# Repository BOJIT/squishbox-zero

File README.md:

# squishbox-zero
MIDI Synthesiser based on https://github.com/GeekFunkLabs/squishbox: adapted for Pi Zero 2W

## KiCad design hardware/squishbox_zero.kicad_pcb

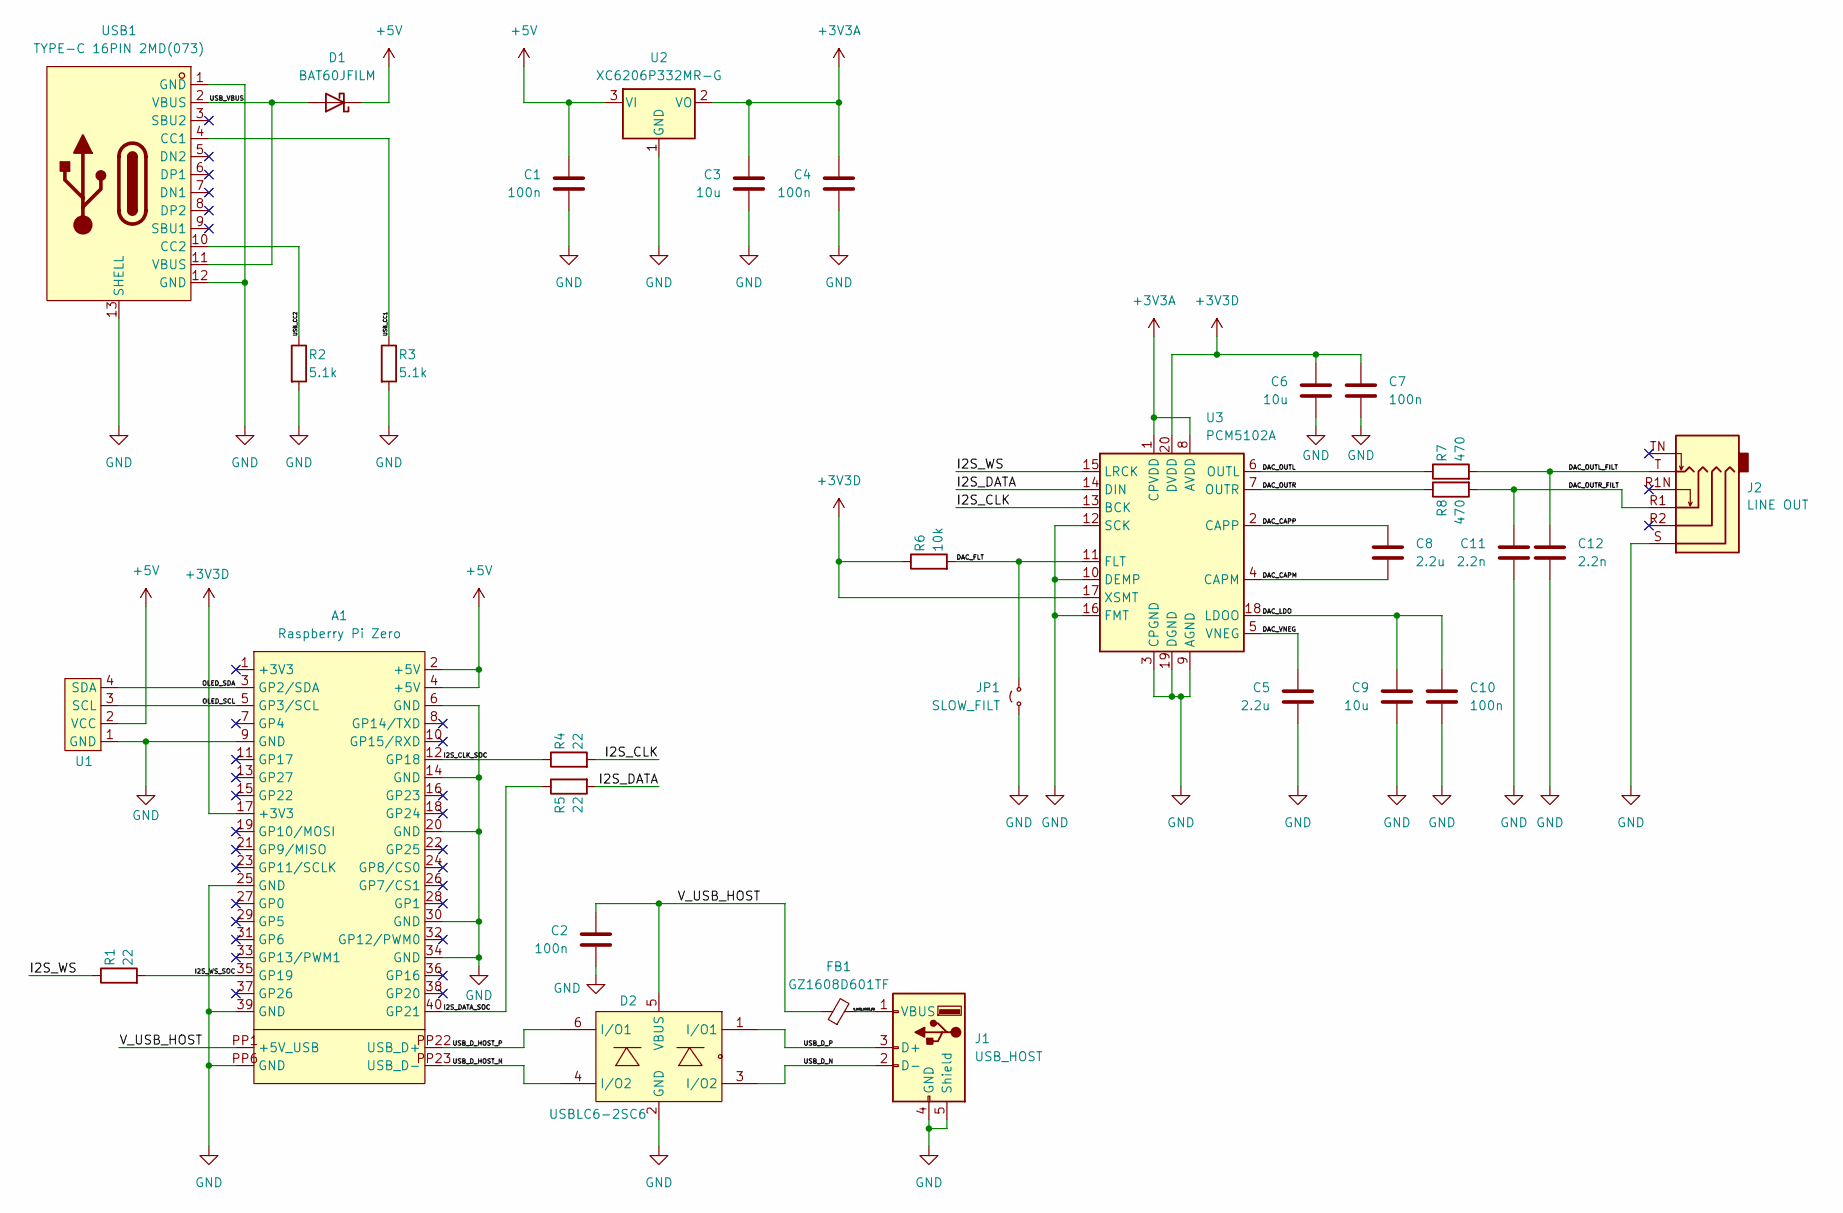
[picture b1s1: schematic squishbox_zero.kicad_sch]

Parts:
A1: Raspberry Pi Zero; Raspberry_Pi_Zero
C1, C2, C4, C7, C10: 100n; C_0402_1005Metric; LCSC Part C1525
C3, C6, C9: 10u; C_0603_1608Metric; LCSC Part C19702
C5, C8: 2.2u; C_0402_1005Metric; LCSC Part C12530
C11, C12: 2.2n; C_0805_2012Metric; LCSC Part C28260
D1: BAT60JFILM; D_SOD-323; LCSC Part C133103
D2: USBLC6-2SC6; SOT-23-6_L2.9-W1.6-P0.95-LS2.8-BL; LCSC Part C7519
FB1: GZ1608D601TF; R_0603_1608Metric; LCSC Part C1002
J1: USB_HOST; USB-A-SMD_USB-M-21; LCSC Part C42474
J2: LINE OUT; AUDIO-SMD_PJ-342; LCSC Part C668606
JP1: SLOW_FILT; SolderJumper-2_P1.3mm_Open_RoundedPad1.0x1.5mm
R1, R4, R5: 22; R_0402_1005Metric; LCSC Part C25092
R2, R3: 5.1k; R_0402_1005Metric; LCSC Part C25905
R6: 10k; R_0402_1005Metric; LCSC Part C25744
R7, R8: 470; R_0402_1005Metric; LCSC Part C25117
U1: SSD1306-0.91-OLED-4pin-128x32
U2: XC6206P332MR-G; SOT-23-3; LCSC Part C5446
U3: PCM5102A; TSSOP-20_4.4x6.5mm_P0.65mm; LCSC Part C107671
USB1: TYPE-C 16PIN 2MD(073); USB-C-SMD_TYPE-C-16PIN; LCSC Part C2765186

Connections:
+3V3A: C3.1, C4.1, U2.2 (VO), U3.1 (CPVDD), U3.8 (AVDD)
+3V3D: A1.17 (+3V3), C6.1, C7.1, R6.1, U3.17 (XSMT), U3.20 (DVDD)
+5V: A1.2 (+5V), A1.4 (+5V), C1.1, D1.1 (K), U1.2 (VCC), U2.3 (VI)
/DAC_CAPM: C8.2, U3.4 (CAPM)
/DAC_CAPP: C8.1, U3.2 (CAPP)
/DAC_FLT: JP1.2 (B), R6.2, U3.11 (FLT)
/DAC_LDO: C9.1, C10.1, U3.18 (LDOO)
/DAC_OUTL: R7.1, U3.6 (OUTL)
/DAC_OUTL_FILT: C12.1, J2.T, R7.2
/DAC_OUTR: R8.1, U3.7 (OUTR)
/DAC_OUTR_FILT: C11.1, J2.R1, R8.2
/DAC_VNEG: C5.1, U3.5 (VNEG)
/I2S_CLK: R4.2, U3.13 (BCK)
/I2S_CLK_SOC: A1.12 (GP18), R4.1
/I2S_DATA: R5.2, U3.14 (DIN)
/I2S_DATA_SOC: A1.40 (GP21), R5.1
/I2S_WS: R1.1, U3.15 (LRCK)
/I2S_WS_SOC: A1.35 (GP19), R1.2
/OLED_SCL: A1.5 (GP3/SCL), U1.3 (SCL)
/OLED_SDA: A1.3 (GP2/SDA), U1.4 (SDA)
/USB_CC1: R3.1, USB1.4 (CC1)
/USB_CC2: R2.1, USB1.10 (CC2)
/USB_D_HOST_N: A1.PP23 (USB_D-), D2.4 (I/O2)
/USB_D_HOST_P: A1.PP22 (USB_D+), D2.6 (I/O1)
/USB_D_N: D2.3 (I/O2), J1.2 (D-)
/USB_D_P: D2.1 (I/O1), J1.3 (D+)
/USB_VBUS: D1.2 (A), USB1.2 (VBUS), USB1.11 (VBUS)
/V_USB_HOST: A1.PP1 (+5V_USB), C2.1, D2.5 (VBUS), FB1.1
/V_USB_HOST_FB: FB1.2, J1.1 (VBUS)
GND: A1.6 (GND), A1.9 (GND), A1.14 (GND), A1.20 (GND), A1.25 (GND), A1.30 (GND), A1.34 (GND), A1.39 (GND), A1.PP6 (GND), C1.2, C2.2, C3.2, C4.2, C5.2, C6.2, C7.2, C9.2, C10.2, C11.2, C12.2, D2.2 (GND), J1.4 (GND), J1.5 (Shield), J2.S, JP1.1 (A), R2.2, R3.2, U1.1 (GND), U2.1 (GND), U3.3 (CPGND), U3.9 (AGND), U3.10 (DEMP), U3.12 (SCK), U3.16 (FMT), U3.19 (DGND), USB1.1 (GND), USB1.12 (GND), USB1.13 (SHELL)

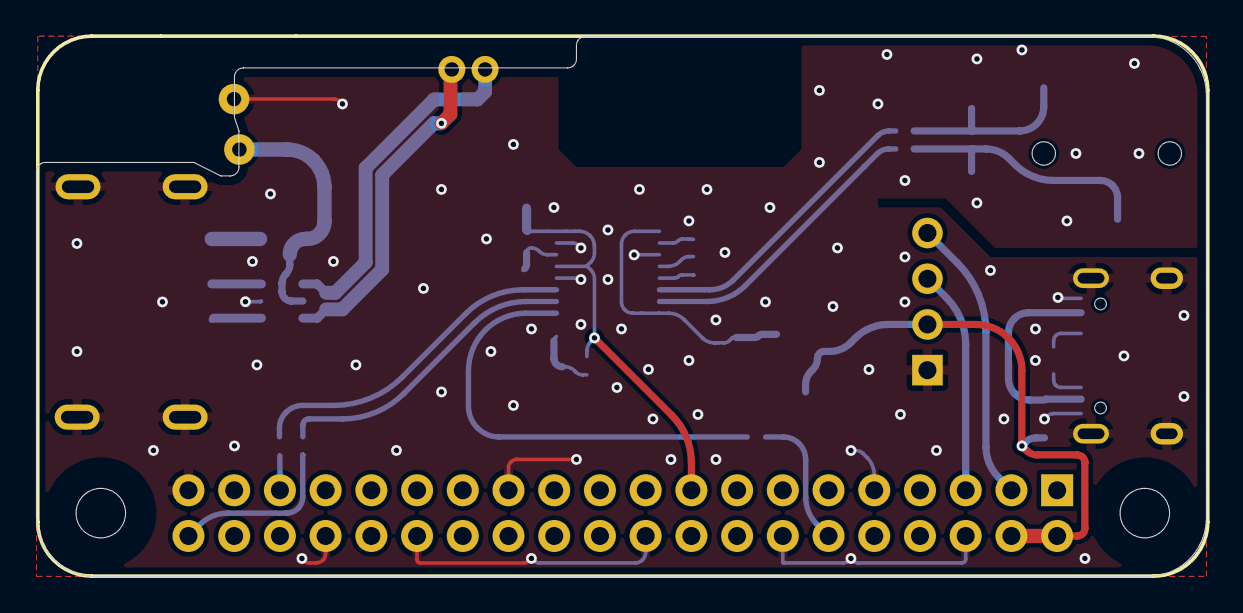
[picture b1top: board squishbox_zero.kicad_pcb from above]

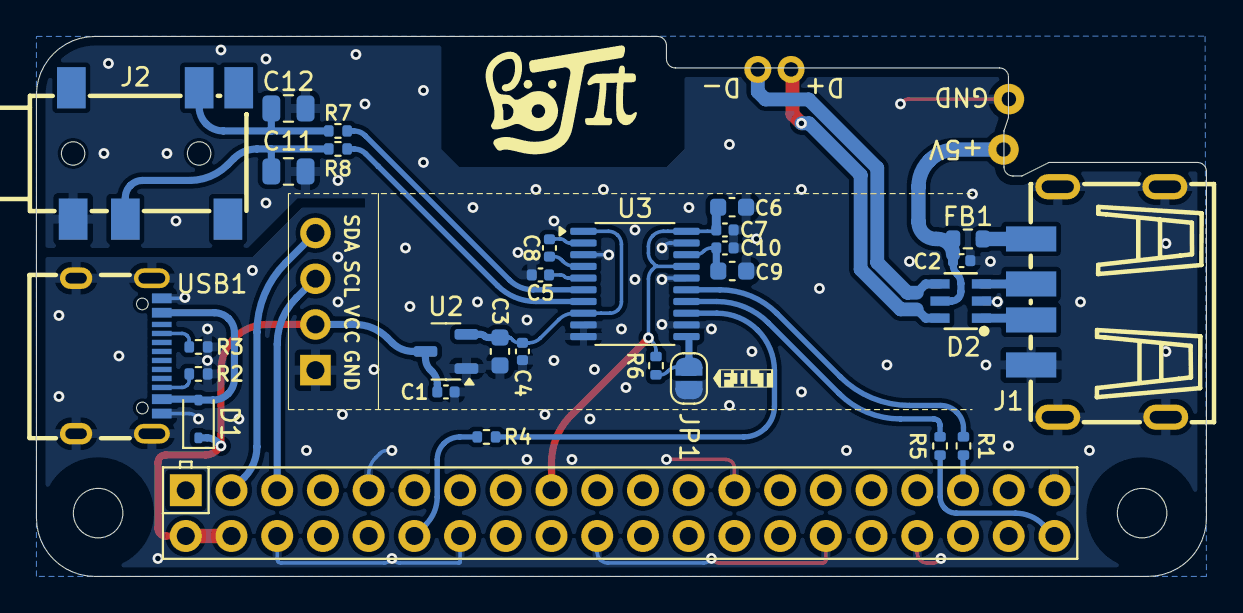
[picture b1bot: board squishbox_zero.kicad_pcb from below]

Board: 2 copper layers, 65.0 x 30.0 mm, 32 parts (32 on the bottom side), 30 nets.

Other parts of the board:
kibuzzard-68B38B7F: G***; kibuzzard-68B38B7F

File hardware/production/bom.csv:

Designator           , Footprint                        , Quantity, Value                , LCSC Part #
"C1, C10, C2, C4, C7", 0402                             ,        5, 100n                 , C1525
"C11, C12"           , 0805                             ,        2, 2.2n                 , C28260
"C3, C6, C9"         , 0603                             ,        3, 10u                  , C19702
"C5, C8"             , 0402                             ,        2, 2.2u                 , C12530
D1                   , D_SOD-323                        ,        1, BAT60JFILM           , C133103
D2                   , SOT-23-6_L2.9-W1.6-P0.95-LS2.8-BL,        1, USBLC6-2SC6          , C7519
FB1                  , 0603                             ,        1, GZ1608D601TF         , C1002
J1                   , USB-A-SMD_USB-M-21               ,        1, USB_HOST             , C42474
J2                   , AUDIO-SMD_PJ-342                 ,        1, LINE OUT             , C668606
"R1, R4, R5"         , 0402                             ,        3, 22                   , C25092
"R2, R3"             , 0402                             ,        2, 5.1k                 , C25905
R6                   , 0402                             ,        1, 10k                  , C25744
"R7, R8"             , 0402                             ,        2, 470                  , C25117
U2                   , SOT-23-3                         ,        1, XC6206P332MR-G       , C5446
U3                   , TSSOP-20_4.4x6.5mm_P0.65mm       ,        1, PCM5102A             , C107671
USB1                 , USB-C-SMD_TYPE-C-16PIN           ,        1, TYPE-C 16PIN 2MD(073), C2765186

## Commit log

2025-08-30 Rough form factor in place
2025-08-30 Audio circuit layout
2025-08-30 LCD + Finalised Schematic
2025-08-30 Routed
2025-08-31 First attempt at fab files
2025-08-31 Fix component orientation
2025-09-17 Enough mods that I can use my keyboard
